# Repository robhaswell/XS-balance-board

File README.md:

# XS-balance-board
An open source multi-battery charging board for use with a 6S balance charger

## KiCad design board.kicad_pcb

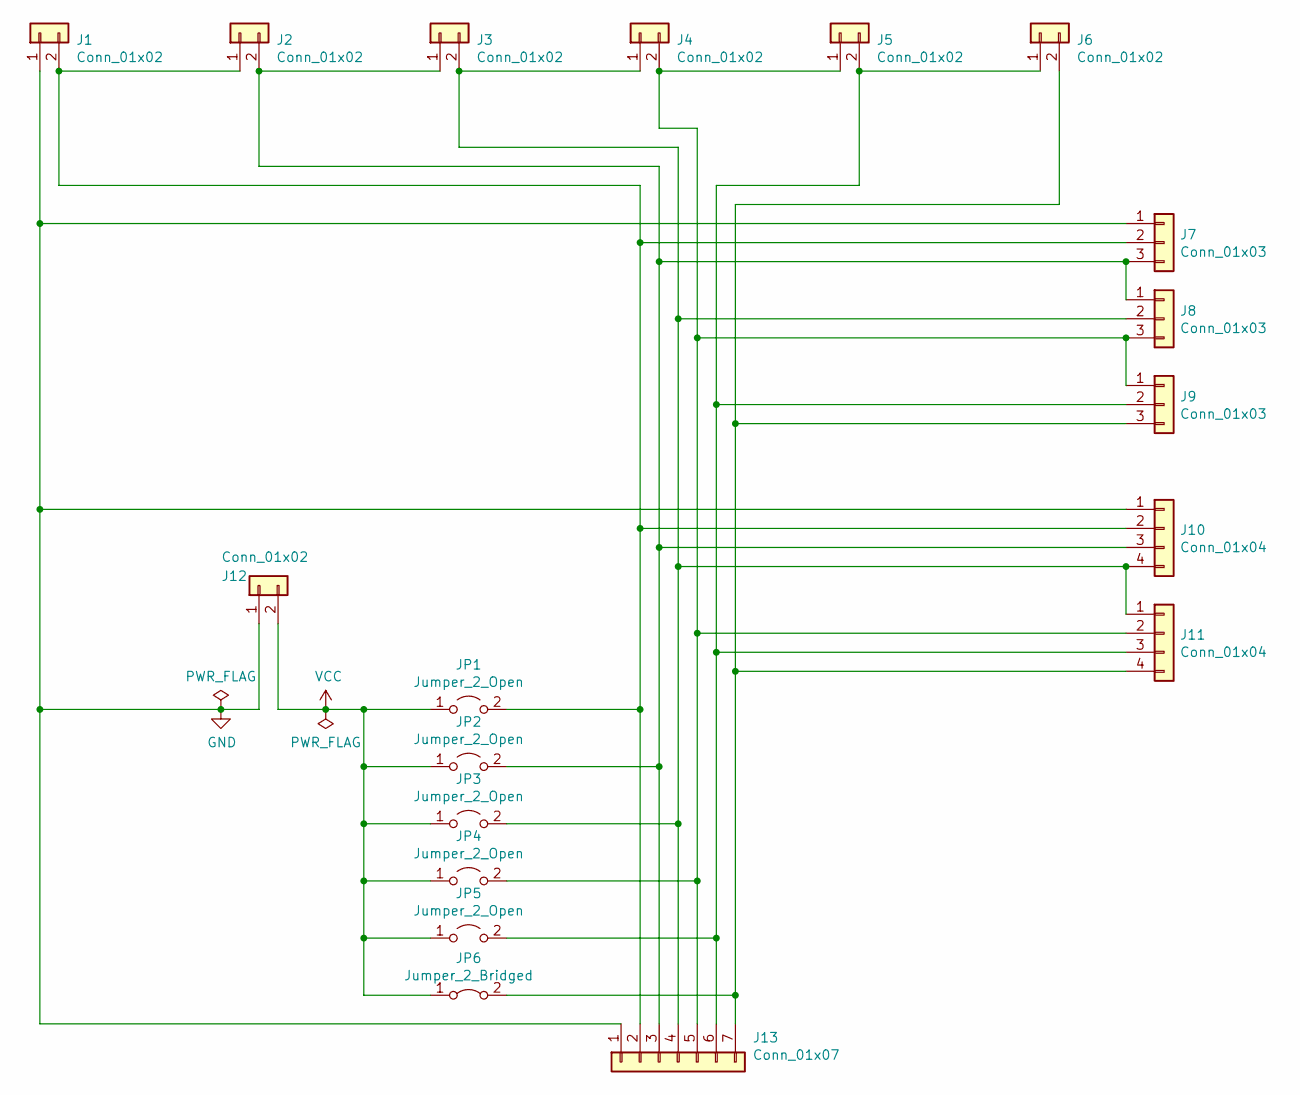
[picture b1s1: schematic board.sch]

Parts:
J1, J2, J3, J4, J5, J6: Conn_01x02; JST_PH_B2B-PH-K_1x02_P2.00mm_Vertical
J7, J8, J9: Conn_01x03; JST_XH_B3B-XH-A_1x03_P2.50mm_Vertical
J10, J11: Conn_01x04; JST_XH_B4B-XH-A_1x04_P2.50mm_Vertical
J12: Conn_01x02; AMASS_XT60-M_1x02_P7.20mm_Vertical
J13: Conn_01x07; JST_XH_B7B-XH-A_1x07_P2.50mm_Vertical
JP1, JP2, JP3, JP4, JP5: Jumper_2_Open; PinHeader_1x02_P2.54mm_Horizontal
JP6: Jumper_2_Bridged; PinHeader_1x02_P2.54mm_Horizontal

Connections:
GND: J1.1, J7.1, J10.1, J12.1, J13.1
unnamed: J1.2, J2.1, J7.2, J10.2, J13.2, JP1.2 (B)
unnamed: J2.2, J3.1, J7.3, J8.1, J10.3, J13.3, JP2.2 (B)
unnamed: J3.2, J4.1, J8.2, J10.4, J11.1, J13.4, JP3.2 (B)
unnamed: J4.2, J5.1, J8.3, J9.1, J11.2, J13.5, JP4.2 (B)
unnamed: J5.2, J6.1, J9.2, J11.3, J13.6, JP5.2 (B)
unnamed: J6.2, J9.3, J11.4, J13.7, JP6.2 (B)
VCC: J12.2, JP1.1 (A), JP2.1 (A), JP3.1 (A), JP4.1 (A), JP5.1 (A), JP6.1 (A)

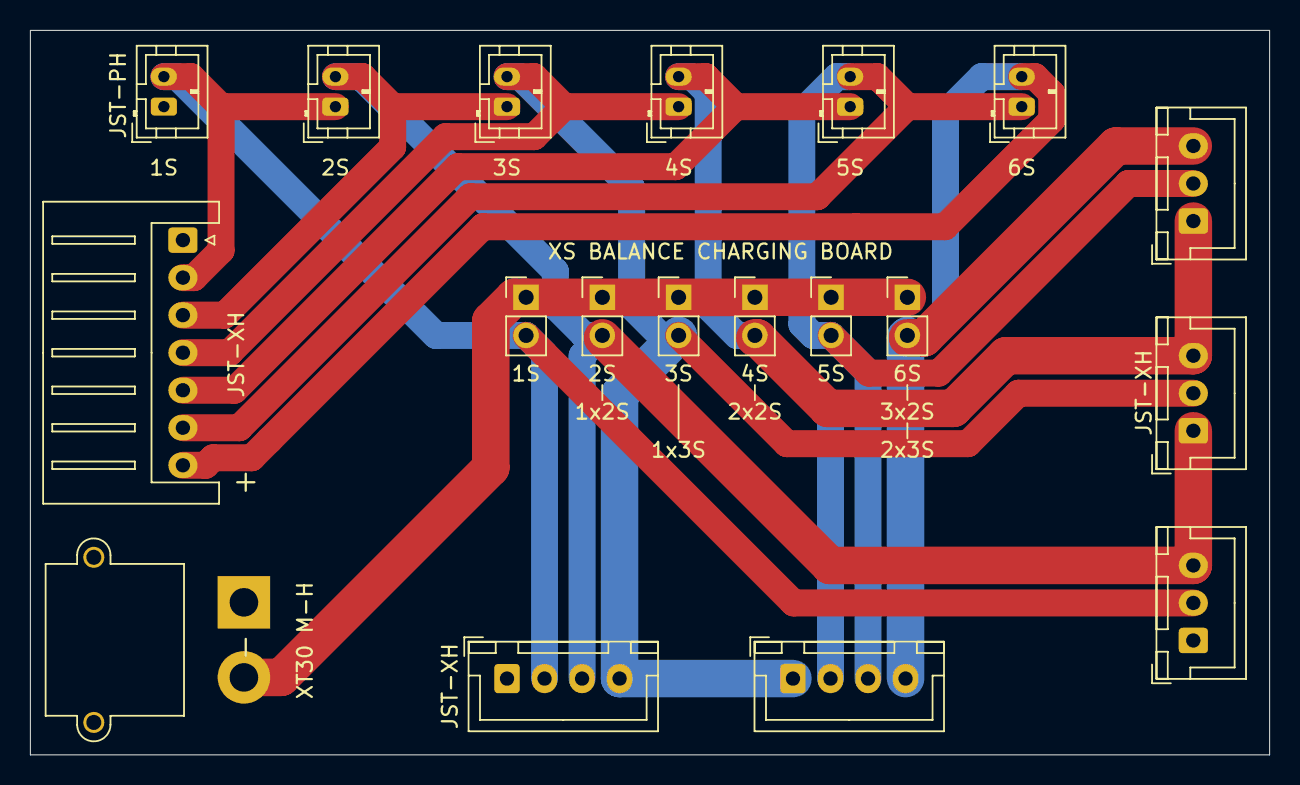
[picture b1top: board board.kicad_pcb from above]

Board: 2 copper layers, 82.5 x 48.3 mm, 19 parts (0 on the bottom side), 8 nets.

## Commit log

2021-07-11 Initial commit.
2021-07-12 New 1s, 2s and 3s design.
2021-07-12 Gerber files.
2021-07-18 Use correct XT30 connector.
